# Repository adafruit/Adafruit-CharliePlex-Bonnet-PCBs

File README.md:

## Adafruit CharliePlex LED Matrix Bonnet PCB

<a href="http://www.adafruit.com/products/3467"><br/>
Click here to purchase one from the Adafruit shop</a>

PCB files for the Adafruit CharliePlex LED Matrix Bonnet. 

Format is EagleCAD schematic and board layout

* https://www.adafruit.com/?q=charlieplex%20bonnet

### Description

You won't be able to look away from the mesmerizing patterns created by this Adafruit CharliePlex LED Matrix Display Bonnet.  This 16x8 LED display can be placed atop any Raspberry Pi computer with a 2x20 connector, for a beautiful, bright grid of 128 charlieplexed LEDs. It even comes with a built-in charlieplex driver that is run over I2C.

We carry these Bonnets in a [few vivid colors](https://www.adafruit.com/?q=charlieplex%20bonnet)

What is particularly nice about this Wing is the I2C LED driver chip has the ability to PWM each individual LED in a 16x8 grid so you can have beautiful LED lighting effects, without a lot of pin twiddling. Simply tell the chip which LED on the grid you want lit, and what brightness and it's all taken care of for you. You get 8-bit (256 level) dimming for each individual LED.

The IS31FL3731 is a nice little chip - and it runs happily over 3.3V power. Inside is enough RAM for 8 separate frames of display memory so you can set up multiple frames of an animation and flip them to be displayed with a single command. Since it uses I2C, it takes up only the SDA/SCL pins on your Pi and can share those pins with other I2C devices and sensors.

Comes fully assembled, no soldering required, so you can plug it in immediately. To program it, [you'll use our CircuitPython library](https://github.com/adafruit/Adafruit_CircuitPython_IS31FL3731), which works with Linux computers like Raspberry Pi. After a pip install, [run some of the examples to display simple graphics or text.](https://github.com/adafruit/Adafruit_CircuitPython_IS31FL3731/tree/master/examples)

### License

Adafruit invests time and resources providing this open source design, please support Adafruit and open-source hardware by purchasing products from [Adafruit](https://www.adafruit.com)!

Designed by Limor Fried/Ladyada for Adafruit Industries.

Creative Commons Attribution/Share-Alike, all text above must be included in any redistribution. See license.txt for additional details.

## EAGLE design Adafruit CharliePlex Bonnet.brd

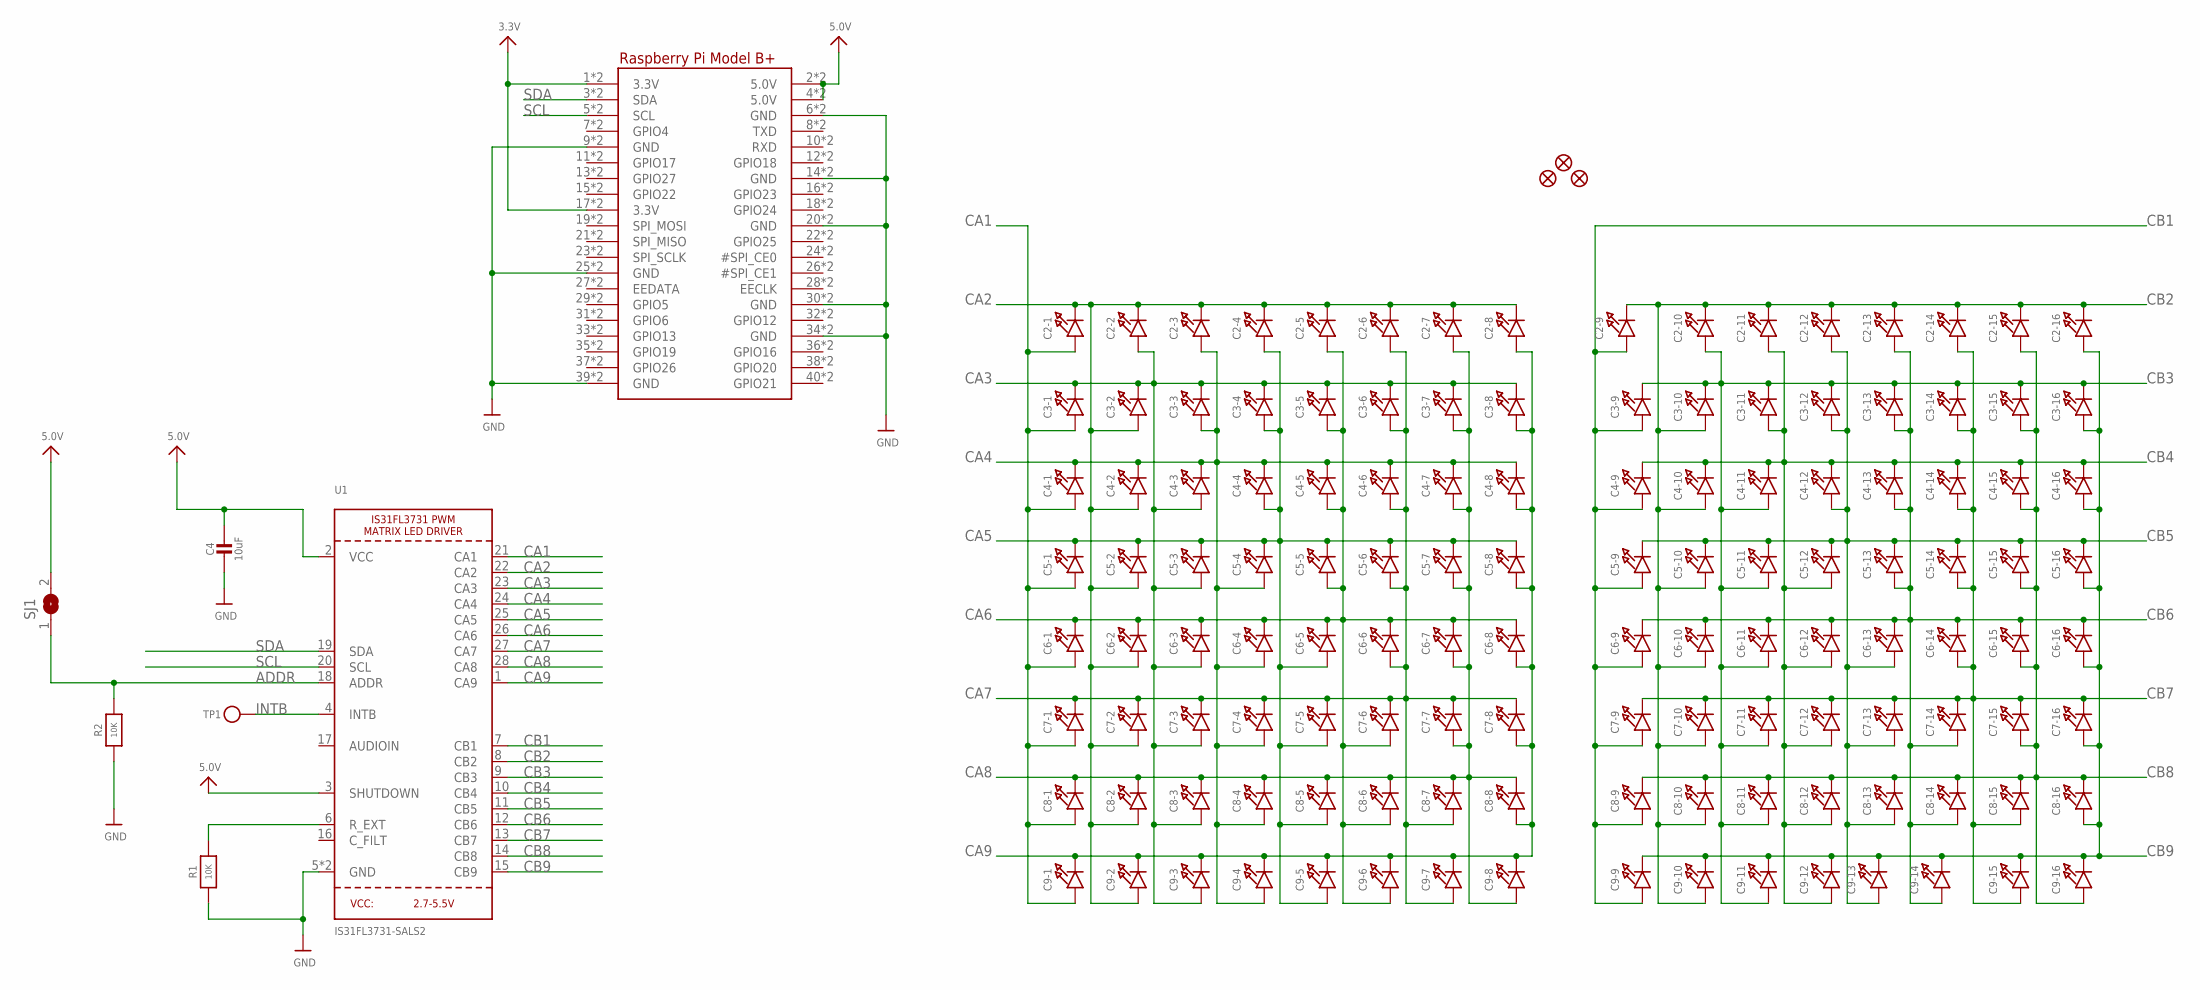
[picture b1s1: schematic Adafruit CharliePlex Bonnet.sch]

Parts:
C2-1, C2-2, C2-3, C2-4, C2-5, C2-6, C2-7, C2-8, C2-9, C2-10, C2-11, C2-12, C2-13, C2-14, C2-15, C2-16, C3-1, C3-2, C3-3, C3-4, C3-5, C3-6, C3-7, C3-8, C3-9, C3-10, C3-11, C3-12, C3-13, C3-14, C3-15, C3-16, C4-1, C4-2, C4-3, C4-4, C4-5, C4-6, C4-7, C4-8, C4-9, C4-10, C4-11, C4-12, C4-13, C4-14, C4-15, C4-16, C5-1, C5-2, C5-3, C5-4, C5-5, C5-6, C5-7, C5-8, C5-9, C5-10, C5-11, C5-12, C5-13, C5-14, C5-15, C5-16, C6-1, C6-2, C6-3, C6-4, C6-5, C6-6, C6-7, C6-8, C6-9, C6-10, C6-11, C6-12, C6-13, C6-14, C6-15, C6-16, C7-1, C7-2, C7-3, C7-4, C7-5, C7-6, C7-7, C7-8, C7-9, C7-10, C7-11, C7-12, C7-13, C7-14, C7-15, C7-16, C8-1, C8-2, C8-3, C8-4, C8-5, C8-6, C8-7, C8-8, C8-9, C8-10, C8-11, C8-12, C8-13, C8-14, C8-15, C8-16, C9-1, C9-2, C9-3, C9-4, C9-5, C9-6, C9-7, C9-8, C9-9, C9-10, C9-11, C9-12, C9-13, C9-14, C9-15, C9-16: LED0603_NOOUTLINE; CHIPLED_0603_NOOUTLINE
C4: 10uF; 0805-NO
FID1, FID2, FID3: FIDUCIAL_1MM
R1, R2: 10K; 0603-NO
RPI1: RASPBERRYPI_BPLUS_BONNET_THMSMT; PI_BONNET_THMSMT
SJ1: SOLDERJUMPER; SOLDERJUMPER_ARROW_NOPASTE
TP1: TESTPOINTROUND1.5MM; TESTPOINT_ROUND_1.5MM
U1: IS31FL3731-SALS2; QFN28_4MM_0.4MM

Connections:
3.3V: RPI1.1 (3.3V), RPI1.17 (3.3V), RPI1.S1 (3.3V), RPI1.S17 (3.3V)
5.0V: C4.1, RPI1.2 (5.0V), RPI1.4 (5.0V), RPI1.S2 (5.0V), RPI1.S4 (5.0V), SJ1.2, U1.2 (VCC), U1.3 (SHUTDOWN)
ADDR: R2.2, SJ1.1, U1.18 (ADDR)
CA1: C2-1.A, C3-1.A, C4-1.A, C5-1.A, C6-1.A, C7-1.A, C8-1.A, C9-1.A, U1.21 (CA1)
CA2: C2-1.C, C2-2.C, C2-3.C, C2-4.C, C2-5.C, C2-6.C, C2-7.C, C2-8.C, C3-2.A, C4-2.A, C5-2.A, C6-2.A, C7-2.A, C8-2.A, C9-2.A, U1.22 (CA2)
CA3: C2-2.A, C3-1.C, C3-2.C, C3-3.C, C3-4.C, C3-5.C, C3-6.C, C3-7.C, C3-8.C, C4-3.A, C5-3.A, C6-3.A, C7-3.A, C8-3.A, C9-3.A, U1.23 (CA3)
CA4: C2-3.A, C3-3.A, C4-1.C, C4-2.C, C4-3.C, C4-4.C, C4-5.C, C4-6.C, C4-7.C, C4-8.C, C5-4.A, C6-4.A, C7-4.A, C8-4.A, C9-4.A, U1.24 (CA4)
CA5: C2-4.A, C3-4.A, C4-4.A, C5-1.C, C5-2.C, C5-3.C, C5-4.C, C5-5.C, C5-6.C, C5-7.C, C5-8.C, C6-5.A, C7-5.A, C8-5.A, C9-5.A, U1.25 (CA5)
CA6: C2-5.A, C3-5.A, C4-5.A, C5-5.A, C6-1.C, C6-2.C, C6-3.C, C6-4.C, C6-5.C, C6-6.C, C6-7.C, C6-8.C, C7-6.A, C8-6.A, C9-6.A, U1.26 (CA6)
CA7: C2-6.A, C3-6.A, C4-6.A, C5-6.A, C6-6.A, C7-1.C, C7-2.C, C7-3.C, C7-4.C, C7-5.C, C7-6.C, C7-7.C, C7-8.C, C8-7.A, C9-7.A, U1.27 (CA7)
CA8: C2-7.A, C3-7.A, C4-7.A, C5-7.A, C6-7.A, C7-7.A, C8-1.C, C8-2.C, C8-3.C, C8-4.C, C8-5.C, C8-6.C, C8-7.C, C8-8.C, C9-8.A, U1.28 (CA8)
CA9: C2-8.A, C3-8.A, C4-8.A, C5-8.A, C6-8.A, C7-8.A, C8-8.A, C9-1.C, C9-2.C, C9-3.C, C9-4.C, C9-5.C, C9-6.C, C9-7.C, C9-8.C, U1.1 (CA9)
CB1: C2-9.A, C3-9.A, C4-9.A, C5-9.A, C6-9.A, C7-9.A, C8-9.A, C9-9.A, U1.7 (CB1)
CB2: C2-9.C, C2-10.C, C2-11.C, C2-12.C, C2-13.C, C2-14.C, C2-15.C, C2-16.C, C3-10.A, C4-10.A, C5-10.A, C6-10.A, C7-10.A, C8-10.A, C9-10.A, U1.8 (CB2)
CB3: C2-10.A, C3-9.C, C3-10.C, C3-11.C, C3-12.C, C3-13.C, C3-14.C, C3-15.C, C3-16.C, C4-11.A, C5-11.A, C6-11.A, C7-11.A, C8-11.A, C9-11.A, U1.9 (CB3)
CB4: C2-11.A, C3-11.A, C4-9.C, C4-10.C, C4-11.C, C4-12.C, C4-13.C, C4-14.C, C4-15.C, C4-16.C, C5-12.A, C6-12.A, C7-12.A, C8-12.A, C9-12.A, U1.10 (CB4)
CB5: C2-12.A, C3-12.A, C4-12.A, C5-9.C, C5-10.C, C5-11.C, C5-12.C, C5-13.C, C5-14.C, C5-15.C, C5-16.C, C6-13.A, C7-13.A, C8-13.A, C9-13.A, U1.11 (CB5)
CB6: C2-13.A, C3-13.A, C4-13.A, C5-13.A, C6-9.C, C6-10.C, C6-11.C, C6-12.C, C6-13.C, C6-14.C, C6-15.C, C6-16.C, C7-14.A, C8-14.A, C9-14.A, U1.12 (CB6)
CB7: C2-14.A, C3-14.A, C4-14.A, C5-14.A, C6-14.A, C7-9.C, C7-10.C, C7-11.C, C7-12.C, C7-13.C, C7-14.C, C7-15.C, C7-16.C, C8-15.A, C9-15.A, U1.13 (CB7)
CB8: C2-15.A, C3-15.A, C4-15.A, C5-15.A, C6-15.A, C7-15.A, C8-9.C, C8-10.C, C8-11.C, C8-12.C, C8-13.C, C8-14.C, C8-15.C, C8-16.C, C9-16.A, U1.14 (CB8)
CB9: C2-16.A, C3-16.A, C4-16.A, C5-16.A, C6-16.A, C7-16.A, C8-16.A, C9-9.C, C9-10.C, C9-11.C, C9-12.C, C9-13.C, C9-14.C, C9-15.C, C9-16.C, U1.15 (CB9)
GND: C4.2, R1.1, R2.1, RPI1.6 (GND), RPI1.9 (GND), RPI1.14 (GND), RPI1.20 (GND), RPI1.25 (GND), RPI1.30 (GND), RPI1.34 (GND), RPI1.39 (GND), RPI1.S6 (GND), RPI1.S9 (GND), RPI1.S14 (GND), RPI1.S20 (GND), RPI1.S25 (GND), RPI1.S30 (GND), RPI1.S34 (GND), RPI1.S39 (GND), U1.5 (GND), U1.THERMAL (GND)
INTB: TP1.P$1, U1.4 (INTB)
R_EXT: R1.2, U1.6 (R_EXT)
SCL: RPI1.5 (SCL), RPI1.S5 (SCL), U1.20 (SCL)
SDA: RPI1.3 (SDA), RPI1.S3 (SDA), U1.19 (SDA)

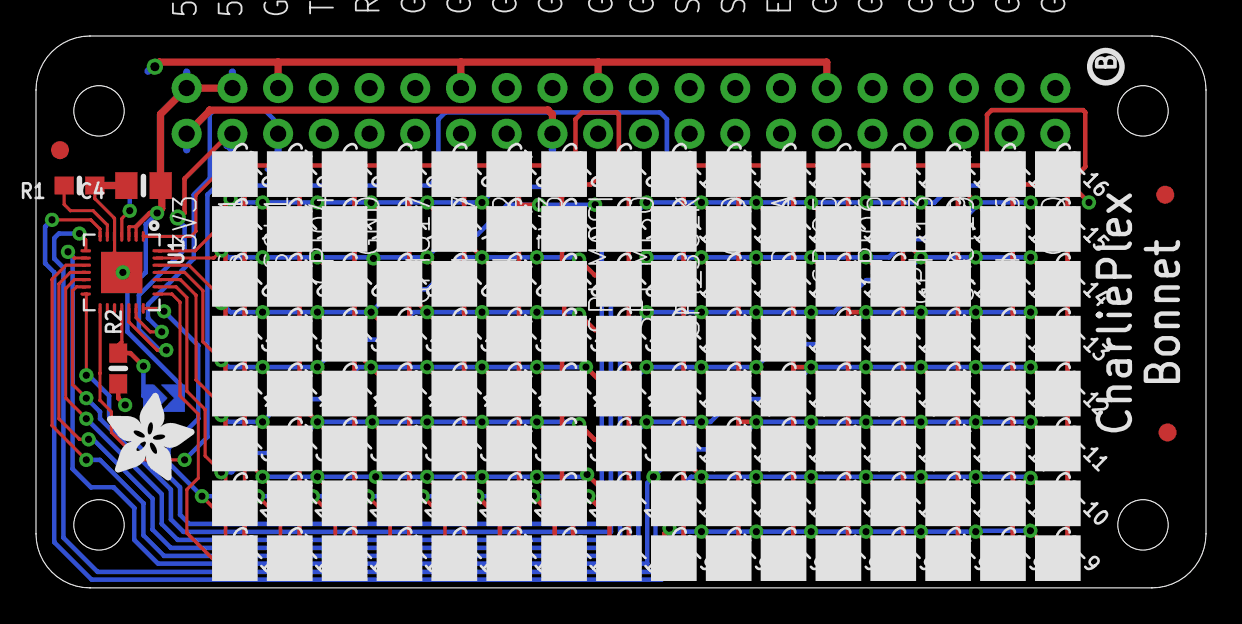
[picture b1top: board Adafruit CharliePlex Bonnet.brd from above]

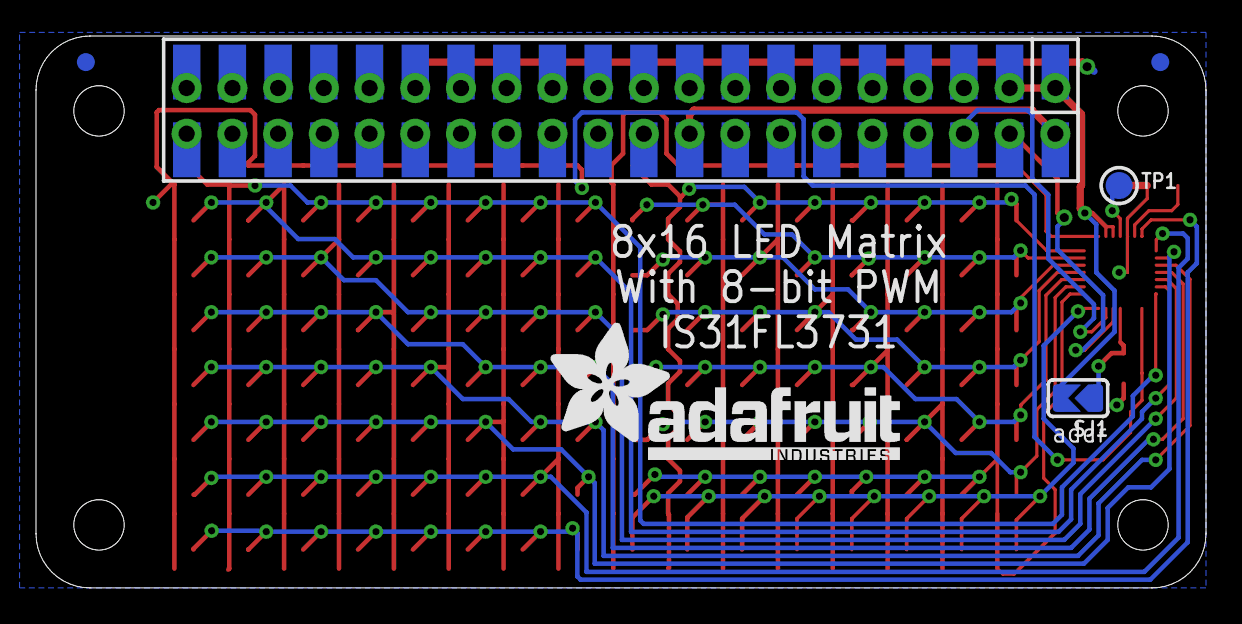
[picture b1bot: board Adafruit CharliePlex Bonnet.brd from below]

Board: 2 copper layers, 65.0 x 30.7 mm, 142 parts (3 on the bottom side), 26 nets.

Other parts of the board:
U$1: ADAFRUIT_5MM
U$2: ADAFRUIT_TEXT_20MM
U$13: CHARLIE_BONNET_GRID
U$14: PCBFEAT-REV-040

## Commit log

2019-03-05 adding PCB files
2019-07-17 updated to use cookiecutter for pcb repos

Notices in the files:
parts and their libraries:
microbuilder: This work is placed in the public domain, and may be freely used for commercial and non-commercial work with the following conditions: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
